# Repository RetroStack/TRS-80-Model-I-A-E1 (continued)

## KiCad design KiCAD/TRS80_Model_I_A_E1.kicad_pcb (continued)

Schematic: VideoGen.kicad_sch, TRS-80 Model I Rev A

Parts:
R40: 4.7k; TRS80_Model_I_R_0.25W
Z8: 74LS153; TRS80_Model_I_DIP16
Z9: 74LS04; TRS80_Model_I_DIP14
Z10, Z11: 74LS166; TRS80_Model_I_DIP16
Z26: 74LS20; TRS80_Model_I_DIP14
Z29: MCM6670; TRS80_Model_I_DIP18
Z30: 74LS02; TRS80_Model_I_DIP14

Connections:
+5V: R40.2, Z8.16 (VCC), Z9.14 (VCC), Z10.16 (VCC), Z11.16 (VCC), Z26.14 (VCC), Z29.18 (VCC); also elsewhere on the board
/Video/Video Counter/L0: Z29.11 (R0); also elsewhere on the board
/Video/Video Counter/L1: Z29.10 (R1); also elsewhere on the board
/Video/Video Counter/L2: Z8.14 (S0), Z29.8 (R2); also elsewhere on the board
/Video/Video Counter/L3: Z8.2 (S1); also elsewhere on the board
/Video/Video Counter/SHIFT: Z9.9; also elsewhere on the board
/Video/Video Counter/~LATCH: Z9.3; also elsewhere on the board
/Video/Video Generator/GRAPHICS: Z26.4; also elsewhere on the board
/Video/Video Generator/LB0: Z8.6 (I0a), Z29.7 (A0); also elsewhere on the board
/Video/Video Generator/LB1: Z8.10 (I0b), Z29.6 (A1); also elsewhere on the board
/Video/Video Generator/LB2: Z8.5 (I1a), Z29.5 (A2); also elsewhere on the board
/Video/Video Generator/LB3: Z8.11 (I1b), Z29.4 (A3); also elsewhere on the board
/Video/Video Generator/LB4: Z8.4 (I2a), Z29.3 (A4); also elsewhere on the board
/Video/Video Generator/LB5: Z8.12 (I2b), Z29.2 (A5); also elsewhere on the board
/Video/Video Generator/LB6: Z29.1 (A6); also elsewhere on the board
/Video/Video Generator/PIXEL: Z30.1; also elsewhere on the board
/Video/Video Generator/~BLANK: Z26.1, Z26.2, Z26.9; also elsewhere on the board
/Video/Video Generator/~CHARGAP: Z26.12; also elsewhere on the board
/Video/Video Generator/~GRAPHICS: Z26.10; also elsewhere on the board
GND: Z8.1 (Ea), Z8.8 (GND), Z8.15 (Eb), Z9.1, Z9.5, Z9.7 (GND), Z9.11, Z9.13, Z10.1 (Ds), Z10.2 (A), Z10.3 (B), Z10.6 (CE), Z10.8 (GND), Z10.14 (H), Z11.1 (Ds), Z11.2 (A), Z11.3 (B), Z11.6 (CE), Z11.8 (GND), Z26.7 (GND), Z29.9 (GND), Z29.17 (~CS); also elsewhere on the board
unnamed: Z10.4 (C), Z29.12 (D0)
unnamed: Z9.8, Z10.7 (Clk), Z11.7 (Clk)
unnamed: R40.1, Z10.9 (Clr), Z11.9 (Clr)
unnamed: Z10.5 (D), Z29.13 (D1)
unnamed: Z10.10 (E), Z29.14 (D2)
unnamed: Z10.11 (F), Z29.15 (D3)
unnamed: Z10.12 (G), Z29.16 (D4)
unnamed: Z10.15 (PE), Z26.8
unnamed: Z10.13 (Qh), Z30.3
unnamed: Z8.9 (Zb), Z11.4 (C), Z11.5 (D), Z11.10 (E)
unnamed: Z8.7 (Za), Z11.11 (F), Z11.12 (G), Z11.14 (H)
unnamed: Z11.15 (PE), Z26.6
unnamed: Z11.13 (Qh), Z30.2
unnamed: Z9.4, Z26.5, Z26.13

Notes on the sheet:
ASCII
SHIFT/~{LOAD}
LATCH
Right
GRAPHICS PIXEL
Left
Character Generator
GRAPHICS
~{SHIFT}
ASCII PIXEL
Inversed Clock (delays clock)

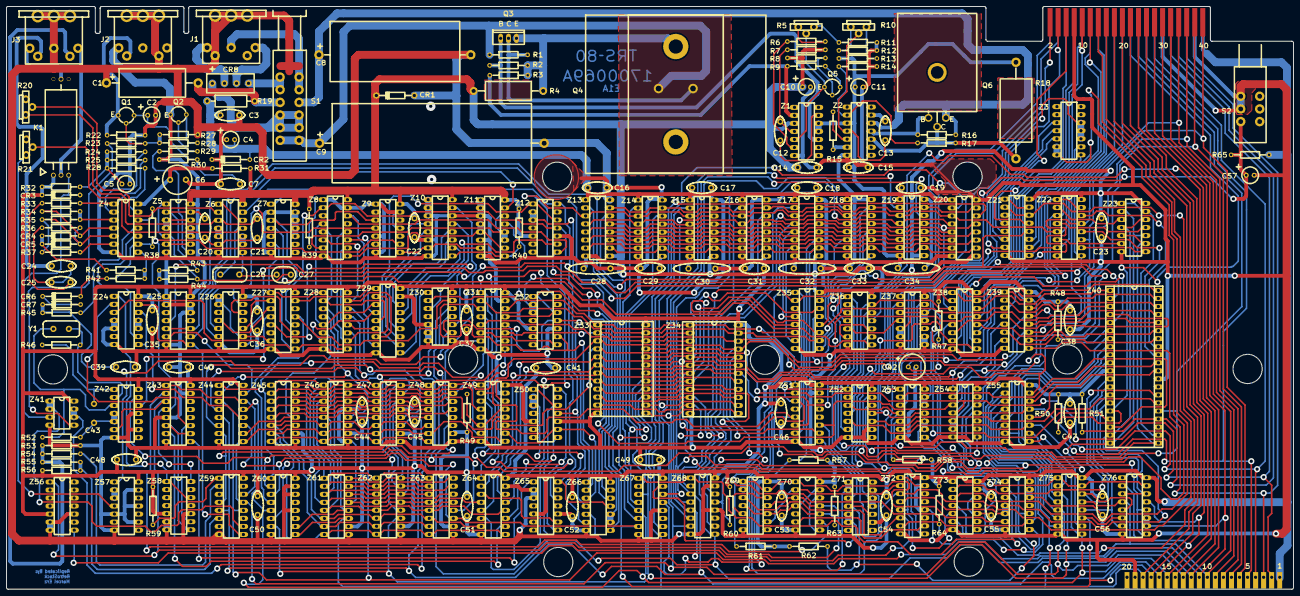
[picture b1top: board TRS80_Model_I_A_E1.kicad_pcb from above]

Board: 2 copper layers, 406.8 x 184.2 mm, 221 parts (0 on the bottom side), 297 nets.
